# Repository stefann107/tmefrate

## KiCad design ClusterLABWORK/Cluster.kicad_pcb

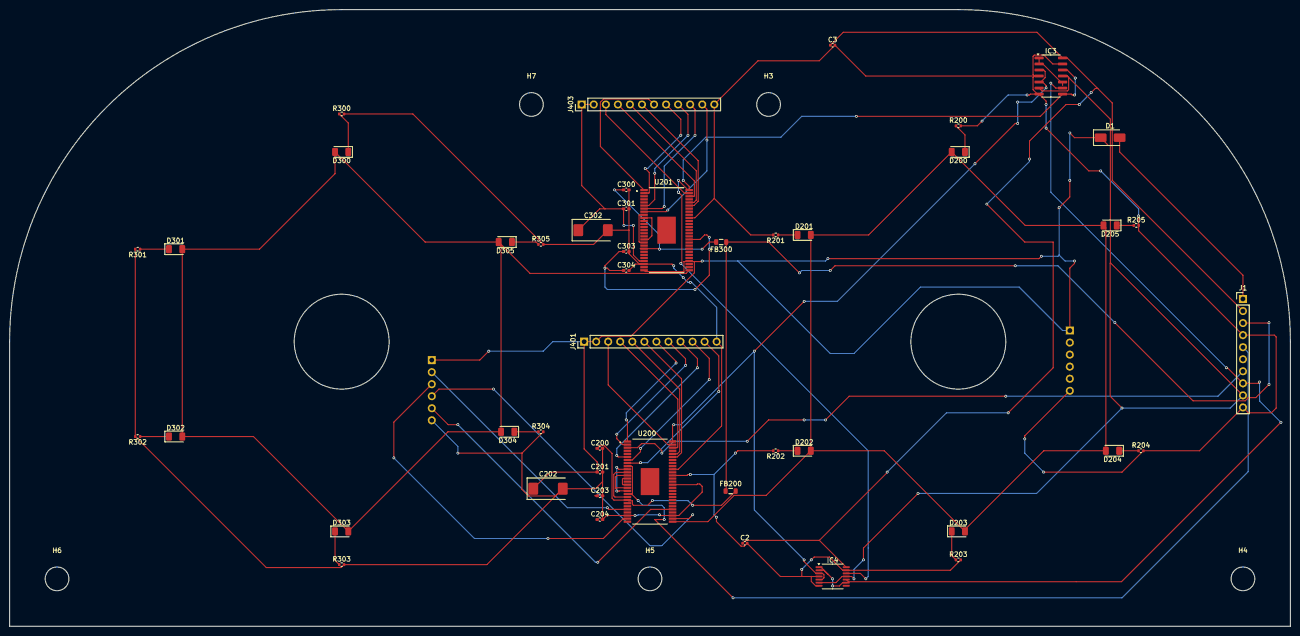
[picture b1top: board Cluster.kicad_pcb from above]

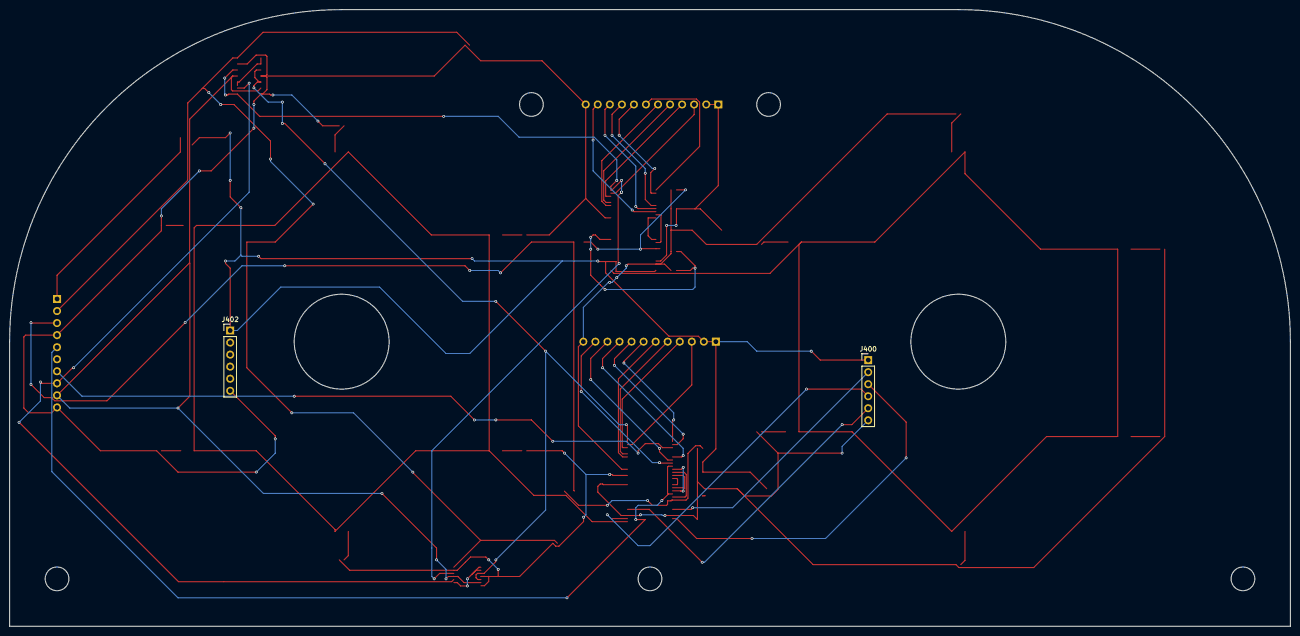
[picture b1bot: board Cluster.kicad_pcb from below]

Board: 2 copper layers, 270.0 x 130.0 mm, 53 parts (2 on the bottom side), 66 nets.

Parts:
C2, C3: 100nF; C_0402_1005Metric
C200, C300: 100pF; C_0402_1005Metric_Pad0.74x0.62mm_HandSolder
C201, C203, C204, C301, C303, C304: 100nF; C_0402_1005Metric_Pad0.74x0.62mm_HandSolder
C202, C302: 330uF; CP_EIA-7343-15_Kemet-W
D1: MRA4003T3G; D_SMA
D200, D201, D202, D203, D204, D205, D300, D301, D302, D303, D304, D305: LED; LED_1206_3216Metric
FB200, FB300: MMZ2012; L_0805_2012Metric
H3, H4, H5, H6, H7: MountingHole; MountingHole_5mm
IC3: SOIC-14_3.9x8.7mm_P1.27mm
IC4: TSSOP-14_4.4x5mm_P0.65mm
J1: Conn_01x10; PinHeader_1x10_P2.54mm_Vertical
J400, J402: Conn_01x06; PinHeader_1x06_P2.54mm_Vertical
J401, J403: Conn_01x12; PinHeader_1x12_P2.54mm_Vertical
R200, R201, R202, R203, R204, R205, R300, R301, R302, R303, R304, R305: 1k2; R_0402_1005Metric
U200, U201: SOP65P1030X245-55N

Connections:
/Input Connectors/J100_RxD: IC3.6 (OUT), IC3.11 (OUT), IC4.6 (OUT), IC4.11 (OUT), J1.9
/Input Connectors/J100_TxD: IC3.1 (OE), IC3.2 (IN), IC3.9 (IN), IC3.10 (OE), IC4.1 (OE), IC4.2 (IN), IC4.9 (IN), IC4.10 (OE), J1.8
/Speedometer/IC200_IC100_PTA0: IC3.3 (OUT), IC3.5 (IN), IC4.3 (OUT), IC4.5 (IN), U200.54 (PTA0/KBD0)
/Speedometer/IC200_J101_HB1: J400.2, U200.23 (HB1)
/Speedometer/IC200_J101_HB2: J400.3, U200.26 (HB2)
/Speedometer/IC200_J101_HB3: J400.4, U200.29 (HB3)
/Speedometer/IC200_J101_HB4: J400.5, U200.32 (HB4)
/Speedometer/IC200_J103_PTA1: J401.3, U200.53 (PTA1/KBD1)
/Speedometer/IC200_J103_PTA2: J401.4, U200.52 (PTA2/KBD2)
/Speedometer/IC200_J103_PTA3: J401.5, U200.50 (PTA3/KBD3)
/Speedometer/IC200_J103_PTA4: J401.6, U200.49 (PTA4/KBD4)
/Speedometer/IC200_J103_PTB3: J401.11, U200.8 (PTB3/AD3)
/Speedometer/IC200_J103_PTB4: J401.10, U200.7 (PTB4/AD4)
/Speedometer/IC200_J103_PTB5: J401.9, U200.6 (PTB5/AD5)
/Speedometer/IC200_J103_PTB6: J401.8, U200.2 (PTB6)
/Speedometer/IC200_J103_PTB7: J401.7, U200.1 (PTB7)
/Speedometer/J100_IC200_PROG_SPEEDO: J1.5, U200.9 (~IRQ), U200.18 (~IRQ_A)
/Speedometer/J100_LIN: FB200.1, FB300.1, J1.3
/Speedometer/J100_OSC: J1.7, U200.3 (PTC4/OSC1), U201.3 (PTC4/OSC1)
/Tachometer/IC300_IC100_PTA0: IC3.8 (OUT), IC3.12 (IN), IC4.8 (OUT), IC4.12 (IN), U201.54 (PTA0/KBD0)
/Tachometer/IC300_J102_HB1: J402.2, U201.23 (HB1)
/Tachometer/IC300_J102_HB2: J402.3, U201.26 (HB2)
/Tachometer/IC300_J102_HB3: J402.4, U201.29 (HB3)
/Tachometer/IC300_J102_HB4: J402.5, U201.32 (HB4)
/Tachometer/IC300_J104_PTA1: J403.3, U201.53 (PTA1/KBD1)
/Tachometer/IC300_J104_PTA2: J403.4, U201.52 (PTA2/KBD2)
/Tachometer/IC300_J104_PTA3: J403.5, U201.50 (PTA3/KBD3)
/Tachometer/IC300_J104_PTA4: J403.6, U201.49 (PTA4/KBD4)
/Tachometer/IC300_J104_PTB3: J403.11, U201.8 (PTB3/AD3)
/Tachometer/IC300_J104_PTB4: J403.10, U201.7 (PTB4/AD4)
/Tachometer/IC300_J104_PTB5: J403.9, U201.6 (PTB5/AD5)
/Tachometer/IC300_J104_PTB6: J403.8, U201.2 (PTB6)
/Tachometer/IC300_J104_PTB7: J403.7, U201.1 (PTB7)
/Tachometer/J100_IC300_PROG_TACHO: J1.6, U201.9 (~IRQ), U201.18 (~IRQ_A)
unnamed: D200.2 (A), D201.2 (A), D202.2 (A), D203.2 (A), D204.2 (A), D205.2 (A), U200.28 (HS)
unnamed: D200.1 (K), R200.1
unnamed: D201.1 (K), R201.1
unnamed: D202.1 (K), R202.1
unnamed: D203.1 (K), R203.1
unnamed: D204.1 (K), R204.1
unnamed: D205.1 (K), R205.1
unnamed: D300.2 (A), D301.2 (A), D302.2 (A), D303.2 (A), D304.2 (A), D305.2 (A), U201.28 (HS)
unnamed: D300.1 (K), R300.1
unnamed: D301.1 (K), R301.1
unnamed: D302.1 (K), R302.1
unnamed: D303.1 (K), R303.1
unnamed: D304.1 (K), R304.1
unnamed: D305.1 (K), R305.1
unnamed: U200.12 (PTD0/TACH0/BEMF), U200.16 (BEMF)
unnamed: C203.1, C204.1, U200.38 (VDD), U200.46 (EVDD), U200.47 (VDDA), U200.48 (VREFH)
unnamed: U200.13 (PTD1/TACH1), U200.15 (FGEN)
unnamed: C200.1, FB200.2, U200.20 (LIN)
unnamed: U200.11 (PTB1/AD1), U200.19 (~SS)
unnamed: U200.41 (RXD), U200.42 (PTE1/RXD)
unnamed: U200.10 (~RST), U200.17 (~RST_A)
unnamed: U201.12 (PTD0/TACH0/BEMF), U201.16 (BEMF)
unnamed: C303.1, C304.1, U201.38 (VDD), U201.46 (EVDD), U201.47 (VDDA), U201.48 (VREFH)
unnamed: U201.13 (PTD1/TACH1), U201.15 (FGEN)
unnamed: C300.1, FB300.2, U201.20 (LIN)
unnamed: U201.11 (PTB1/AD1), U201.19 (~SS)
unnamed: U201.41 (RXD), U201.42 (PTE1/RXD)
unnamed: U201.10 (~RST), U201.17 (~RST_A)
VBAT+: D1.2 (A), J1.1
VBAT-: C2.2, C3.2, C200.2, C201.2, C202.2, C203.2, C204.2, C300.2, C301.2, C302.2, C303.2, C304.2, IC3.4 (OE), IC3.7 (GND), IC3.13 (OE), IC4.4 (OE), IC4.7 (GND), IC4.13 (OE), J1.4, J1.10, J400.6, J401.12, J402.6, J403.12, R200.2, R201.2, R202.2, R203.2, R204.2, R205.2, R300.2, R301.2, R302.2, R303.2, R304.2, R305.2, U200.25 (GND1), U200.30 (GND2), U200.40 (VSS), U200.43 (VREFL), U200.44 (VSSA), U200.45 (EVSS), U201.25 (GND1), U201.30 (GND2), U201.40 (VSS), U201.43 (VREFL), U201.44 (VSSA), U201.45 (EVSS)
VPROG: C2.1, C3.1, IC3.14 (VCC), IC4.14 (VCC), J1.2
VSUP: C201.1, C202.1, C301.1, C302.1, D1.1 (K), J400.1, J401.1, J401.2, J402.1, J403.1, J403.2, U200.24 (VSUP1), U200.27 (VSUP2), U200.31 (VSUP3), U201.24 (VSUP1), U201.27 (VSUP2), U201.31 (VSUP3)

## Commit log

2026-04-28 Add files via upload
    nono
2026-05-05 Add files via upload
    ultimu lab updatat cum ar veni
